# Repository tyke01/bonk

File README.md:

# BONK

**An open-source handheld RC transmitter built around the ESP32.**
Designed by Spectral Systems.

> **Status: Rev 1 (first PCB revision).** The schematic passes ERC with 0 errors and the PCB passes DRC. Boards have been ordered but **not yet assembled or tested**, so expect errata. See [Known issues](#known-issues-rev-1) before building one.

---

## Contents

- [Features](#features)
- [Repository layout](#repository-layout)
- [Hardware overview](#hardware-overview)
- [Power architecture](#power-architecture)
- [ESP32 pin map](#esp32-pin-map)
- [Buses and addresses](#buses-and-addresses)
- [Firmware notes](#firmware-notes)
- [Bill of materials](#bill-of-materials)
- [Manufacturing](#manufacturing)
- [Assembly](#assembly)
- [Bring-up checklist](#bring-up-checklist)
- [Known issues (Rev 1)](#known-issues-rev-1)
- [License](#license)

---

## Features

- **MCU:** ESP32 module (Ai-Thinker ESP32-SL) with on-board PCB antenna
- **Inputs:** 2 analog joysticks, 2 potentiometers, 2 toggle switches, a rotary encoder with push switch, and BOOT/EN buttons
- **Display:** 2.8" ILI9341 320x240 SPI TFT module (its SD card slot is not used)
- **Radio:** nRF24L01 breakout on the shared SPI bus. ESP-NOW/WiFi/BLE are also available from the ESP32 itself
- **USB-C:** programming and charging through a CP2102N USB-UART bridge with automatic reset into the bootloader
- **Battery:** 2x 18650 cells in parallel (1S), with a TP4056 charger, DW01A + FS8205A protection, and USB/battery load sharing
- **Battery monitoring:** INA226 voltage and current monitor on I2C, which measures both charge and discharge current
- **PCB:** 4 layers, 125 x 100 mm, 1.6 mm thick

---

## Repository layout

```
RC controller.kicad_pro     KiCad project
RC controller.kicad_sch     Schematic (single sheet, with design notes)
RC controller.kicad_pcb     PCB layout
RC controller.png           3D render
bom/
  ibom.html                 Interactive BOM (open in a browser for assembly)
  RC controller.csv         Raw BOM export
production/
  RC_controller.zip         Gerbers + drill files, ready to upload to JLCPCB
  bom.csv                   BOM for JLCPCB assembly
  positions.csv             Pick-and-place (CPL) file
  designators.csv
  netlist.ipc               IPC netlist (lets the fab run electrical tests)
placement/
  RC controller-all.pos     KiCad component placement file
```

Designed in **KiCad 10.0.6**. Open `RC controller.kicad_pro` to view everything.

---

## Hardware overview

| Block | Main parts | Notes |
|---|---|---|
| MCU | L1 ESP32-SL | Antenna overhangs the bottom board edge |
| USB-UART | U8 CP2102N (QFN-24), Q1/Q2 BC817 | DTR/RTS drive EN and IO0 for automatic bootloader entry |
| USB-C | X1 GCT USB4085-GF-A, U7 USBLC6-2SC6 | 5.1k pull-downs on CC1/CC2 (sink, default 5 V). USBLC6 provides ESD protection on D+/D- |
| Charger | U6 TP4056 (ESOP-8) | About 1.1 A charge current, set by R24 |
| Protection | U9 DW01A, Q4 FS8205A | Disconnects the cells on overcharge, overdischarge, or overcurrent |
| Load sharing | Q3 AO3401A, D3 SS34 | Runs the system from USB when plugged in, otherwise from the battery |
| Regulator | U2 AP2112K-3.3 | 600 mA LDO, single 3.3 V rail for everything |
| Battery monitor | U3 INA226, R11 20 mΩ | I2C address 0x40 |
| Display | U1 ILI9341 2.8" SPI module | Powered from 3.3 V |
| Radio | U10 nRF24L01 breakout | Shares the SPI bus with the display |
| Sticks | U4/U5 SparkFun COM-09032 | Powered from 3.3 V |
| Pots | RV1/RV2 | Powered from 3.3 V |
| Encoder | S1 Bourns PEC12R-4217F-S0024 | 10k pull-ups plus 10k/10 nF RC hardware debounce |
| Toggles | S2/S3 Würth 472123010111 | Switch to GND |
| Buttons | SW3 (EN/reset), SW4 (BOOT) | R18/C13 delay the release of EN at power-up |
| Battery holder | BT1 Keystone 1048 | 2x 18650, **mounted on the bottom side** |

---

## Power architecture

### Net names

| Net | What it is |
|---|---|
| `+5V` | USB VBUS |
| `+VBAT_IN` | Cell positive terminal |
| `BAT_P` | Battery positive after the shunt. Charger output and Q3 drain connect here |
| `+VBAT_OUT` | **System rail (VSYS).** Feeds the 3.3 V regulator |
| `+3V3` | Regulated 3.3 V for all logic |
| `BAT-` | Raw cell negative |
| `GND` | System ground (the switched negative, P-). Connected to `BAT-` through Q4 |

### Charging path

`TP4056 BAT → BAT_P → R11 shunt → +VBAT_IN → cells → BAT- → Q4 (FS8205A) → GND → back to the TP4056`

The return path goes through the protection MOSFETs. That's what allows the DW01A to stop charging if a cell reaches its overcharge limit.

### Load sharing

- **USB connected:** 5 V feeds `+VBAT_OUT` through D3 (about 4.5 V). Q3's gate sits at 5 V, so Q3 is off, and its body diode is reverse biased. The battery is isolated from the load and only the charger talks to it. Charge termination is therefore not confused by system current.
- **USB disconnected:** R27 pulls Q3's gate to GND, Q3 turns on, and the battery powers `+VBAT_OUT` through Q3's low channel resistance. D3 blocks the battery from back-feeding the USB side.
- **During the handover,** Q3's body diode keeps the rail up so the ESP32 doesn't brown out.

### Protection

The DW01A watches the cell voltage and the voltage drop across the FS8205A. If it detects overcharge, overdischarge, or overcurrent, it turns off one of the two MOSFETs and disconnects `BAT-` from `GND`. R26 only feeds the DW01A's CS sense pin and carries no load current.

### Battery monitoring

R11 (20 mΩ) is in series with the battery, so the INA226 sees both directions of current:

- **Positive current = discharging**
- **Negative current = charging**

The full-scale range is about ±4 A (81.92 mV / 20 mΩ). The INA226's Vin+/Vin- traces are Kelvin-connected directly at R11's pads.

---

## ESP32 pin map

| GPIO | Module pin | Net | Function |
|---|---|---|---|
| 36 (SENSOR_VP) | 4 | `JL_LR` | Left stick X |
| 39 (SENSOR_VN) | 5 | `JL_UD` | Left stick Y (throttle) |
| 34 | 6 | `JR_LR` | Right stick X |
| 35 | 7 | `JR_UD` | Right stick Y |
| 32 | 8 | `POT_L` | Left potentiometer |
| 33 | 9 | `POT_R` | Right potentiometer |
| 25 | 10 | `SW_L` | Left toggle switch (to GND) |
| 26 | 11 | `SW_R` | Right toggle switch (to GND) |
| 27 | 12 | `CLK` | Encoder channel A |
| 14 | 13 | `DT` | Encoder channel B |
| 16 | 27 | `SW` | Encoder push switch (to GND) |
| 13 | 16 | `LED` | TFT backlight |
| 15 | 23 | `CS` | TFT chip select |
| 2 | 24 | `DC` | TFT data/command |
| 5 | 29 | `CSN` | nRF24 chip select |
| 4 | 26 | `CE` | nRF24 chip enable |
| 18 | 30 | `SCK` | SPI clock (through R7, 50 Ω) |
| 19 | 31 | `MISO` | SPI MISO (through R6, 50 Ω) |
| 23 | 37 | `MOSI` | SPI MOSI |
| 21 | 33 | `SDA` | I2C data |
| 22 | 36 | `SCL` | I2C clock |
| 1 (TXD0) | 35 | | To CP2102N RXD |
| 3 (RXD0) | 34 | | From CP2102N TXD |
| 0 | 25 | `BOOT` | BOOT button and auto-reset |
| EN | 3 | `RST` | Reset button, auto-reset, and TFT reset |

**Unused:** IO12 and IO17. The SD0 to SD3, CMD and CLK pins are reserved for the module's flash and must stay unconnected.

**Why these pins:**

- All analog inputs (sticks and pots) are on **ADC1** pins, because ADC2 can't be used while WiFi (including ESP-NOW) is active.
- GPIO34 to 39 are **input-only with no internal pull-ups**, which makes them a good fit for the analog sticks.
- IO0, IO2, IO5, IO12 and IO15 are **strapping pins**. Nothing on the board forces them to a level that would break booting. IO12 is deliberately left unconnected.

---

## Buses and addresses

### SPI (shared)

| Device | Chip select | Other pins |
|---|---|---|
| ILI9341 TFT | IO15 (`CS`) | DC = IO2, reset = EN, backlight = IO13 |
| nRF24L01 | IO5 (`CSN`) | CE = IO4, IRQ not connected |

SCK = IO18, MOSI = IO23, MISO = IO19. Only one device is selected at a time.

### I2C

| Device | Address | Pull-ups |
|---|---|---|
| INA226 | 0x40 (A0 = A1 = GND) | R9/R10, 4.7k to 3.3 V |

---

## Firmware notes

Firmware is developed separately with **PlatformIO** (Arduino framework). The following points are for anyone writing firmware for this board:

- **Toggle switches and the encoder push switch** (IO25, IO26, IO16) have **no external pull-ups**. Use `INPUT_PULLUP`. A closed switch reads LOW.
- **Encoder A/B** (IO27, IO14) already have 10k external pull-ups and RC debounce.
- **TFT_eSPI configuration:** MISO 19, MOSI 23, SCLK 18, CS 15, DC 2, RST -1 (tied to EN), backlight 13. The breadboard prototype used `setRotation(3)`; check that this still fits the PCB orientation.
- **INA226:** address 0x40, shunt 0.020 Ω. Discharge reads positive, charging reads negative.
- **Low-battery cutoff:** the AP2112K is an LDO. Once the battery falls below roughly 3.5 V, the 3.3 V rail starts following it down. Use the INA226 bus voltage to warn the user, and shut down before the DW01A's overdischarge protection trips.
- **Uploading:** the CP2102N's DTR/RTS lines drive EN and IO0 through Q1/Q2, so uploads should start automatically. If they don't, hold BOOT, tap EN, then release BOOT.

---

## Bill of materials

LCSC numbers are the parts matched for the Rev 1 JLCPCB order. **Stock and part numbers change, so verify each one before ordering.** Full BOM files are in `bom/` and `production/`.

| Designator | Value | Package | LCSC | Assembled by |
|---|---|---|---|---|
| C1, C2 | 10 nF 50 V X7R | 0603 | C57112 | JLC |
| C3, C5, C7, C9, C10, C14, C17 | 100 nF 50 V X7R | 0603 | C14663 | JLC |
| C11 | 4.7 µF 16 V X5R | 0603 | C19666 | JLC |
| C12, C13 | 1 µF 50 V X5R | 0603 | C15849 | JLC |
| C4, C6, C8, C15, C16 | 10 µF 10 V X5R | 0603 | C19702 | JLC |
| D1, D2, D4, D5 | LED, green | 0603 | C2289 (verify colour and Vf) | JLC |
| D3 | SS34 Schottky | SMA | C8678 | JLC |
| Q1, Q2 | BC817 NPN | SOT-23 | C22400355 | JLC |
| Q3 | AO3401A P-FET | SOT-23 | C15127 | JLC |
| Q4 | FS8205A dual N-FET | **TSSOP-8** | Choose a TSSOP-8 variant (see Known issues) | JLC |
| R2-R5, R18-R21 | 10k 1% | 0603 | C25804 | JLC |
| R6, R7 | 50 Ω | 0603 | C849792 | JLC |
| R8, R12 | 470 Ω 1% | 0603 | C23179 | JLC |
| R9, R10 | 4.7k 1% | 0603 | C23162 | JLC |
| R11 | 20 mΩ 1% 1 W current sense | 1206 | C7420010 | JLC |
| R13, R22, R23, R26 | 1k 1% | 0603 | C21190 | JLC |
| R14 | 47.5k 1% | 0603 | C137715 | JLC |
| R15 | 22.1k 1% | 0603 | C2960862 | JLC |
| R16, R17 | 5.1k 1% | 0603 | C23186 | JLC |
| R24 | 1.1k 1% | 0603 | C54531154 | JLC |
| R25 | 100 Ω 1% | 0603 | C22775 | JLC |
| R27 | 100k 1% | 0603 | C25803 | JLC |
| U2 | AP2112K-3.3 | SOT-23-5 | C23380830 | JLC |
| U3 | INA226 | VSSOP-10 | C49851 | JLC |
| U6 | TP4056 | ESOP-8 | C16581 | JLC |
| U7 | USBLC6-2SC6 | SOT-23-6 | C2827654 | JLC |
| U8 | CP2102N-A02-GQFN24 | QFN-24 4x4 | C969151 | JLC |
| U9 | DW01A | SOT-23-6 | C351410 | JLC |
| L1 | ESP32-SL module | SMD module | C2764058 | Hand (was out of stock) |
| X1 | USB4085-GF-A USB-C | Through-hole | C7095263 | Hand |
| S1 | PEC12R-4217F-S0024 encoder | Through-hole | C49671241 | Hand |
| S2, S3 | 472123010111 toggle | Through-hole | C20040218 | Hand |
| U4, U5 | SparkFun COM-09032 joystick | Through-hole | C3283715 | Hand |
| RV1, RV2 | Potentiometer | Vishay T93YA footprint | | Hand |
| SW3, SW4 | Tactile switch 6 mm | Through-hole | | Hand |
| U1 | 2.8" ILI9341 SPI TFT module | Header | | Hand |
| U10 | nRF24L01 breakout | 2x4 header | | Hand |
| BT1 | Keystone 1048 2x 18650 holder | SMD, bottom side | | Hand |

---

## Manufacturing

Fabricated at **JLCPCB**. Upload `production/RC_controller.zip`.

| Setting | Value |
|---|---|
| Layers | 4 |
| Size | 125 x 100 mm |
| Thickness | 1.6 mm |
| Outer copper | 1 oz |
| Surface finish | HASL works for hand soldering. ENIG is better for the 0.5 mm pitch parts (U3, U8) |

**Stackup:**

| Layer | Use |
|---|---|
| F.Cu | Signals and components, with GND pour |
| In1.Cu | Solid GND plane |
| In2.Cu | GND plane |
| B.Cu | Signals, plus the battery holder |

**Design rules used:** 0.2 mm default tracks and clearance, 0.5 mm power tracks, 1.0 mm battery tracks, 0.6/0.3 mm vias. USB D+/D- are routed as a differential pair over the In1 GND plane. There is a copper keepout under the ESP32 antenna on all layers.

**Notes:**

- The USB-C connector (X1) has very fine pin spacing, so the board allows bridged solder-mask openings between its pads. Take care not to bridge pins when soldering it.
- U6 (TP4056) uses a modified footprint with 0.3 mm thermal vias, and pad B12 on X1 has a solid zone connection. Both changes are stored on the board, so don't run "Update Footprints from Library" on U6 or X1 without reapplying them.

---

## Assembly

The Rev 1 order uses **JLCPCB partial assembly**: JLC places the SMT parts on the top side, and the rest is hand-soldered.

**Before ordering assembly:**

1. **Q4 must be a TSSOP-8 part.** JLC's automatic match picked a SOT-23-6 FS8205A, which will not fit the footprint. Open the part details and confirm the package.
2. **Check every rotation** in the placement preview: U8, U3, U6, U9, U2, U7, Q1 to Q4, D3 (cathode band) and the LEDs. Compare each part's pin 1 with the pin-1 mark on the silkscreen.
3. **Mounting holes H1 to H4** appear in the CPL but not in the BOM. JLC warns about this; it's safe to continue.

**Hand-soldering order (suggested):**

1. ESP32-SL module (L1)
2. USB-C connector (X1)
3. Battery holder (BT1, bottom side)
4. Buttons, toggles, encoder, pots
5. Joysticks
6. Display and nRF24 headers last, since they cover other parts

The interactive BOM (`bom/ibom.html`) highlights where each part goes.

---

## Bring-up checklist

Work through this in order, and **don't insert the cells until step 4.**

1. **Visual inspection.** Look for solder bridges, especially on U8, U3 and X1.
2. **Short-circuit check (power off).** Measure resistance from GND to `+5V`, `+VBAT_OUT`, `+3V3` and `BAT_P`. None of them should read close to 0 Ω.
3. **USB power, no cells, ideally before soldering the ESP32.** Use a current-limited supply or a USB power meter if you have one. Expect:
   - `+5V` ≈ 5 V
   - `+VBAT_OUT` ≈ 4.5 V (5 V minus the SS34 drop)
   - `+3V3` ≈ 3.3 V
4. **Insert the cells.** Check polarity. **Both cells must be at about the same voltage before you insert them**, because cells in parallel at different voltages push a large current into each other. If the board doesn't run from the battery after you insert the cells, plug in USB once: some DW01-based circuits need a charger connection to leave the protected state.
5. **Charging.** With USB connected, the charge LED should light, and the INA226 should report a negative current.
6. **USB-UART.** Connect to a PC and confirm the CP2102N appears as a serial port. Older systems may need Silicon Labs' CP210x driver.
7. **Firmware.** Upload a test sketch. Uploads should start without pressing BOOT, thanks to auto-reset.
8. **Peripherals, one at a time:** display, sticks and pots, switches and encoder, INA226, nRF24.

---

## Known issues (Rev 1)

- **Q4 package:** see [Assembly](#assembly). Make sure a TSSOP-8 FS8205A is placed.
- **No dedicated bulk capacitor at the nRF24.** nRF24L01 modules are known to need a local bulk capacitor for stable operation. If the radio is unreliable, solder a 10 to 100 µF capacitor across the module's VCC and GND pins. Add a footprint for it in Rev 2.
- **10 µF capacitors are 10 V, 0603.** At 5 V, DC bias derating significantly reduces their effective capacitance. Consider 16 V or higher, or 0805, in Rev 2.
- **Shared MISO.** The ILI9341 and the nRF24 share MISO. Some ILI9341 modules reportedly don't release MISO when deselected, which can corrupt nRF24 reads. If this happens, disconnect the display's MISO; the display only needs MISO for read-back.
- **3.3 V regulation at low battery.** The AP2112K is an LDO, so below about 3.5 V battery the 3.3 V rail drops with it. Handle this with a firmware cutoff.
- **R6/R7 = 50 Ω** is a non-standard value (0.1% thin-film part). 51 Ω works the same and is cheaper to source.
- **LED forward voltage.** D1 and D2 are powered from 3.3 V through 470 Ω. Pick LEDs with a forward voltage around 2 V. Some "green" 0603 LEDs are about 3 V and will be very dim at 3.3 V.

---

## License

The hardware design files are licensed under the **CERN Open Hardware Licence Version 2, Permissive (CERN-OHL-P-2.0)**. See the `LICENSE` file.

Under this licence you may use, study, modify, make and sell the design, as long as you keep the copyright and licence notices. Firmware, once published, will be licensed separately.

---

## Credits

Designed by **Victor Macharia (Syb0rg)**, Spectral Systems.
Repository: [github.com/tyke01/bonk](https://github.com/tyke01/bonk)

Contributions, issue reports, and build photos are welcome. Please open an issue if you build one.

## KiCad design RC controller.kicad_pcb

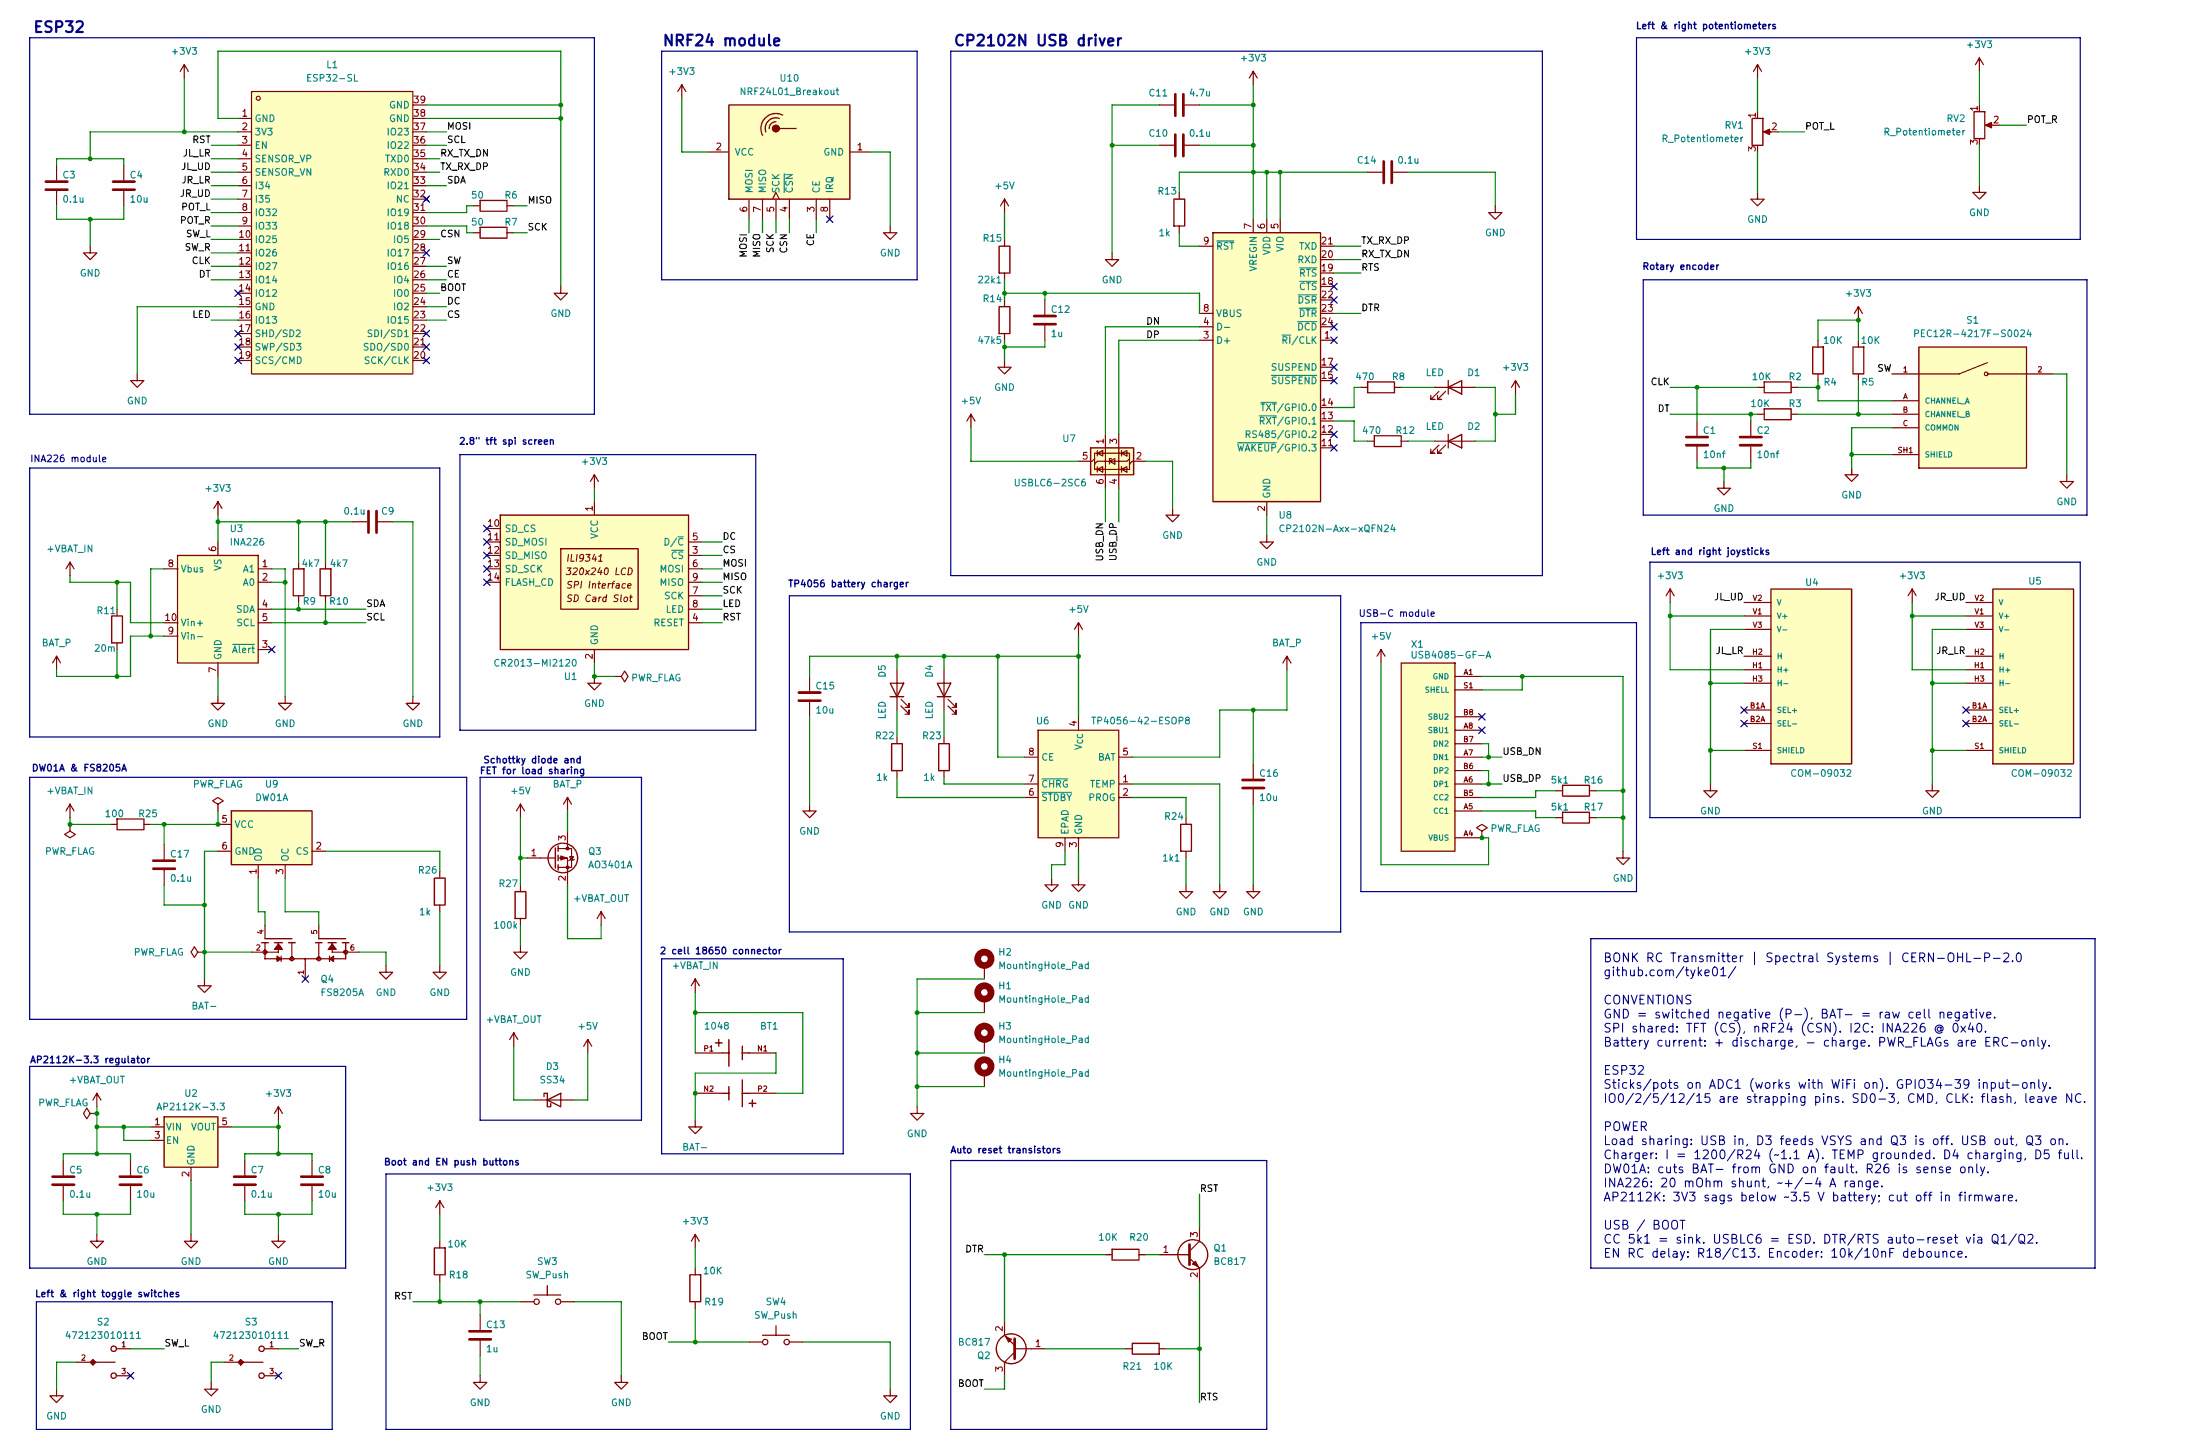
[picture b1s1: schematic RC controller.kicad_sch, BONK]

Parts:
BT1: 1048; Battery_Holder_18650_2_Cell_SMD; PARTREV A
C1, C2: 10nf; C_0603_1608Metric
C3, C5, C7, C9, C10, C14, C17: 0.1u; C_0603_1608Metric
C4, C6, C8, C15, C16: 10u; C_0603_1608Metric
C11: 4.7u; C_0603_1608Metric
C12, C13: 1u; C_0603_1608Metric
D1, D2, D4, D5: LED; LED_0603_1608Metric_Pad1.05x0.95mm_HandSolder
D3: SS34; D_SMA
H1, H2, H3, H4: MountingHole_Pad; MountingHole_3.5mm_Pad
L1: ESP32-SL; WIFIM-SMD_ESP32-SL; MPN ESP32-SL; LCSC Part C2764058
Q1, Q2: BC817; SOT-23
Q3: AO3401A; SOT-23
Q4: FS8205A; SOP65P640X120-8N; PARTREV 1.7
R2, R3, R4, R5, R18, R19, R20, R21: 10K; R_0603_1608Metric
R6, R7: 50; R_0603_1608Metric
R8, R12: 470; R_0603_1608Metric
R9, R10: 4k7; R_0603_1608Metric
R11: 20m; R_1206_3216Metric_Pad1.30x1.75mm_HandSolder
R13, R22, R23, R26: 1k; R_0603_1608Metric
R14: 47k5; R_0603_1608Metric
R15: 22k1; R_0603_1608Metric
R16, R17: 5k1; R_0603_1608Metric
R24: 1k1; R_0603_1608Metric
R25: 100; R_0603_1608Metric
R27: 100k; R_0603_1608Metric
RV1, RV2: R_Potentiometer; Potentiometer_Vishay_T93YA_Vertical
S1: PEC12R-4217F-S0024; XDCR_PEC12R-4217F-S0024; PARTREV 07/21
S2, S3: 472123010111; toggle_switch
SW3, SW4: SW_Push; SW_PUSH_6mm_H7.3mm
U1: CR2013-MI2120
U2: AP2112K-3.3; SOT-23-5
U3: INA226; TSSOP-10_3x3mm_P0.5mm
U4, U5: COM-09032; XDCR_COM-09032; PARTREV N/A
U6: TP4056-42-ESOP8; SOIC-8-1EP_3.9x4.9mm_P1.27mm_EP2.41x3.3mm_ThermalVias
U7: USBLC6-2SC6; SOT-23-6
U8: CP2102N-Axx-xQFN24; QFN-24-1EP_4x4mm_P0.5mm_EP2.6x2.6mm
U9: DW01A; SOT-23-6
U10: NRF24L01_Breakout; nRF24L01_Breakout
X1: USB4085-GF-A; USB4085_CONNECTOR

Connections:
+3V3: C3.1, C4.1, C7.1, C8.1, C9.2, C10.2, C11.2, C14.1, D1.2 (A), D2.2 (A), L1.2 (3V3), R4.2, R5.2, R9.2, R10.2, R13.1, R18.2, R19.2, RV1.1, RV2.1, U1.1 (VCC), U2.5 (VOUT), U3.6 (VS), U4.H1 (H+), U4.V1 (V+), U5.H1 (H+), U5.V1 (V+), U8.5 (VIO), U8.6 (VDD), U8.7 (VREGIN), U10.2 (VCC)
+5V: C15.1, D3.2 (A), D4.2 (A), D5.2 (A), Q3.1 (G), R15.1, R27.1, U6.4 (V_{CC}), U6.8 (CE), U7.5 (VBUS), X1.A4 (VBUS), X1.A9 (VBUS), X1.B4 (VBUS), X1.B9 (VBUS)
+VBAT_IN: BT1.P1, BT1.P2, R11.1, R25.2, U3.10 (Vin+)
+VBAT_OUT: C5.1, C6.1, D3.1 (K), Q3.2 (S), U2.1 (VIN), U2.3 (EN)
/BOOT: L1.25 (IO0), Q2.3 (C), R19.1, SW4.1
/CE: L1.26 (IO4), U10.3 (CE)
/CLK: C1.1, L1.12 (IO27), R2.2
/CS: L1.23 (IO15), U1.3 (~CS)
/CSN: L1.29 (IO5), U10.4 (~CSN)
/DC: L1.24 (IO2), U1.5 (D/~C)
/DN: U7.1 (I/O1), U8.4 (D-)
/DP: U7.3 (I/O2), U8.3 (D+)
/DT: C2.1, L1.13 (IO14), R3.2
/DTR: Q2.2 (E), R20.2, U8.23 (~DTR)
/JL_LR: L1.4 (SENSOR_VP), U4.H2 (H)
/JL_UD: L1.5 (SENSOR_VN), U4.V2 (V)
/JR_LR: L1.6 (I34), U5.H2 (H)
/JR_UD: L1.7 (I35), U5.V2 (V)
/LED: L1.16 (IO13), U1.8 (LED)
/MISO: R6.1, U1.9 (MISO), U10.7 (MISO)
/MOSI: L1.37 (IO23), U1.6 (MOSI), U10.6 (MOSI)
/POT_L: L1.8 (IO32), RV1.2
/POT_R: L1.9 (IO33), RV2.2
/RST: C13.1, L1.3 (EN), Q1.3 (C), R18.1, SW3.1, U1.4 (RESET)
/RTS: Q1.2 (E), R21.2, U8.19 (~RTS)
/RX_TX_DN: L1.35 (TXD0), U8.20 (RXD)
/SCK: R7.1, U1.7 (SCK), U10.5 (SCK)
/SCL: L1.36 (IO22), R10.1, U3.5 (SCL)
/SDA: L1.33 (IO21), R9.1, U3.4 (SDA)
/SW: L1.27 (IO16), S1.1
/SW_L: L1.10 (IO25), S2.1
/SW_R: L1.11 (IO26), S3.1
/TX_RX_DP: L1.34 (RXD0), U8.21 (TXD)
/USB_DN: U7.6 (I/O1), X1.A7 (DN1), X1.B7 (DN2)
/USB_DP: U7.4 (I/O2), X1.A6 (DP1), X1.B6 (DP2)
BAT-: BT1.N1, BT1.N2, C17.2, Q4.2, Q4.3, U9.6 (GND)
BAT_P: C16.1, Q3.3 (D), R11.2, U3.8 (Vbus), U3.9 (Vin-), U6.5 (BAT)
GND: C1.2, C2.2, C3.2, C4.2, C5.2, C6.2, C7.2, C8.2, C9.1, C10.1, C11.1, C12.2, C13.2, C14.2, C15.2, C16.2, H1.1 (1_1), H2.1 (1_1), H3.1 (1_1), H4.1 (1_1), L1.1 (GND), L1.15 (GND), L1.38 (GND), L1.39 (GND), Q4.6, Q4.7, R14.2, R16.1, R17.1, R24.2, R26.2, R27.2, RV1.3, RV2.3, S1.2, S1.C (COMMON), S1.SH1 (SHIELD), S1.SH2 (SHIELD), S2.2, S3.2, SW3.2, SW4.2, U1.2 (GND), U2.2 (GND), U3.1 (A1), U3.2 (A0), U3.7 (GND), U4.H3 (H-), U4.S1 (SHIELD), U4.S2 (SHIELD), U4.S3 (SHIELD), U4.S4 (SHIELD), U4.V3 (V-), U5.H3 (H-), U5.S1 (SHIELD), U5.S2 (SHIELD), U5.S3 (SHIELD), U5.S4 (SHIELD), U5.V3 (V-), U6.1 (TEMP), U6.3 (GND), U6.9 (EPAD), U7.2 (GND), U8.2 (GND), U8.25 (GND), U10.1 (GND), X1.A1 (GND), X1.A12 (GND), X1.B1 (GND), X1.B12 (GND), X1.S1 (SHELL), X1.S2 (SHELL), X1.S3 (SHELL), X1.S4 (SHELL)
unnamed: D1.1 (K), R8.1
unnamed: D2.1 (K), R12.1
unnamed: D4.1 (K), R23.1
unnamed: D5.1 (K), R22.1
unnamed: L1.30 (IO18), R7.2
unnamed: L1.31 (IO19), R6.2
unnamed: Q1.1 (B), R20.1
unnamed: Q2.1 (B), R21.1
unnamed: R2.1, R4.1, S1.A (CHANNEL_A)
unnamed: R3.1, R5.1, S1.B (CHANNEL_B)
unnamed: R24.1, U6.2 (PROG)
unnamed: R23.2, U6.7 (~CHRG)
unnamed: R22.2, U6.6 (~STDBY)
unnamed: C12.1, R14.1, R15.2, U8.8 (VBUS)
unnamed: R13.2, U8.9 (~RST)
unnamed: R12.2, U8.13 (~RXT/GPIO.1)
unnamed: R8.2, U8.14 (~TXT/GPIO.0)
unnamed: R26.1, U9.2 (CS)
unnamed: Q4.5, U9.3 (OC)
unnamed: Q4.4, U9.1 (OD)
unnamed: C17.1, R25.1, U9.5 (VCC)
unnamed: R17.2, X1.A5 (CC1)
unnamed: R16.2, X1.B5 (CC2)

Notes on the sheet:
2.8" tft spi screen
USB-C module
NRF24 module
Left and right joysticks
Schottky diode and FET for load sharing
Rotary encoder
AP2112K-3.3 regulator
CP2102N USB driver
Left & right toggle switches
2 cell 18650 connector
DW01A & FS8205A
ESP32
Boot and EN push buttons
BONK RC Transmitter | Spectral Systems | CERN-OHL-P-2.0 github.com/tyke01/ CONVENTIONS GND = switched negative (P-), BAT- = raw cell negative. SPI shared: TFT (CS), nRF24 (CSN). I2C: INA226 @ 0x40. Battery current: + discharge, - charge. PWR_FLAGs are ERC-only. ESP32 Sticks/pots on ADC1 (works with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
Left & right potentiometers
INA226 module
TP4056 battery charger
Auto reset transistors

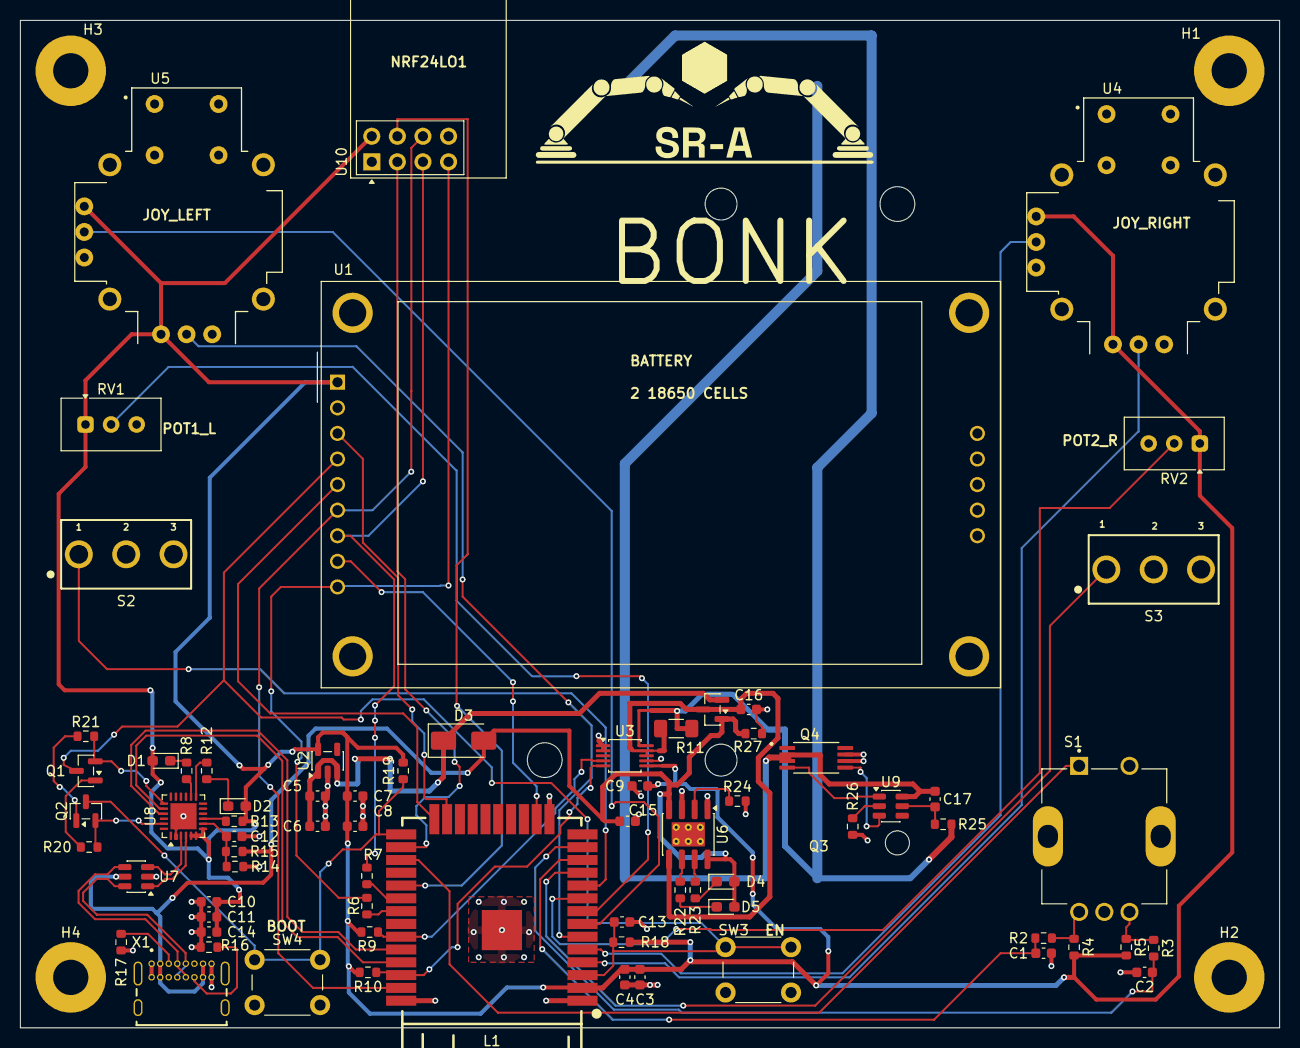
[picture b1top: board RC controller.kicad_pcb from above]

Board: 4 copper layers, 125.0 x 100.0 mm, 76 parts (1 on the bottom side), 61 nets.

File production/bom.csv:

Designator,Footprint,Quantity,Value,LCSC Part #
BT1,Battery_Holder_18650_2_Cell_SMD,1,1048,
"C1, C2",0603,2,10nf,
"C10, C14, C17, C3, C5, C7, C9",0603,7,0.1u,
C11,0603,1,4.7u,
"C12, C13",0603,2,1u,
"C15, C16, C4, C6, C8",0603,5,10u,
"D1, D2, D4, D5",0603,4,LED,
D3,D_SMA,1,SS34,
L1,WIFIM-SMD_ESP32-SL,1,ESP32-SL,C2764058
"Q1, Q2",SOT-23,2,BC817,
Q3,SOT-23,1,AO3401A,
Q4,SOP65P640X120-8N,1,FS8205A,
"R10, R9",0603,2,4k7,
R11,1206,1,20m,
"R12, R8",0603,2,470,
"R13, R22, R23, R26",0603,4,1k,
R14,0603,1,47k5,
R15,0603,1,22k1,
"R16, R17",0603,2,5k1,
"R18, R19, R2, R20, R21, R3, R4, R5",0603,8,10K,
R24,0603,1,1k1,
R25,0603,1,100,
R27,0603,1,100k,
"R6, R7",0603,2,50,
"RV1, RV2",Potentiometer_Vishay_T93YA_Vertical,2,R_Potentiometer,
S1,XDCR_PEC12R-4217F-S0024,1,PEC12R-4217F-S0024,
"S2, S3",toggle_switch,2,472123010111,
"SW3, SW4",SW_PUSH_6mm_H7.3mm,2,SW_Push,
U1,CR2013-MI2120,1,CR2013-MI2120,
U10,nRF24L01_Breakout,1,NRF24L01_Breakout,
U2,SOT-23-5,1,AP2112K-3.3,
U3,TSSOP-10_3x3mm_P0.5mm,1,INA226,
"U4, U5",XDCR_COM-09032,2,COM-09032,
U6,SOIC-8-1EP_3.9x4.9mm_P1.27mm_EP2.41x3.3mm_ThermalVias,1,TP4056-42-ESOP8,
U7,SOT-23-6,1,USBLC6-2SC6,
U8,QFN-24-1EP_4x4mm_P0.5mm_EP2.6x2.6mm,1,CP2102N-Axx-xQFN24,
U9,SOT-23-6,1,DW01A,
X1,USB4085_CONNECTOR,1,USB4085-GF-A,
